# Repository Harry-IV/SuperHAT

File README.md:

# SuperHAT V2

A HAT (hardware attached on top) for the Raspberry Pi 4 & 5. 

---

## Power Rail Breakdown

SuperHAT receives external 5V and 12V power (with a common ground) from an [MR30 connector](https://www.tme.com/us/en-us/details/mr30pw-m/dc-power-connectors/amass/). 12V is used for tools and motors. 5V is used for tools, servos, and powering the Raspberry Pi. When using the SuperHAT, do not plug in a USB-C power supply. 

---

## Feature Overview

1. **Four** N-type MOSFETs for GPIO switching 5V or 12V tools.
2. **Six** connectors for I²C interfacing.
3. **One** dual H-bridge 12V motor driver.
4. **One** stepper motor driver
5. **Two** 5V servo connectors
6. Overvoltage Protection
7. Voltage & Current Sensing

### 1. MOSFET GPIO Switching

#### Schematic

#### N-Type MOSFET

The N-type MOSFET ([AOSS32136C](https://www.digikey.com/en/products/detail/alpha-omega-semiconductor-inc/AOSS32136C/11567433)) in the schematic is routed for low-side switching. When testing, switching on the high side (before the load), resulted in a voltage drop. In an underwater environment, employing low-side switching means that the wires leading to the tool will be high (5V or 12V) when the tool is idling. 

#### Back-EMF Protection

There is a standard diode ([GSD2004WS-HE3-08](https://www.digikey.com/en/products/detail/vishay-general-semiconductor-diodes-division/GSD2004WS-HE3-08/4831745?s=N4IgjCBcpgbFoDGUBmBDANgZwKYBoQB7KAbRABYAGSgJnIgKtoHZmQBdAgBwBcoQAyjwBOASwB2AcxABfArACcCEMkjps%2BIqQqUFAZn0dufSIJETpckAFZmlZavW4CxSGSrN9ADiMhe-ITEpWQIwBVYHVExnLTcQPTgFMBpff1NAixDwBS8laBUojRdte3YrGhpYCHzHaM1XMjAAAgA1JoABJrBqJoBbAEFUkxAAYUIAVy4MHAATAFVxUR4AeRQAWRw0LHHhHCyAWngaqBFx%2Bu0UsoJ9lOPIU-O46w4Zcu0Z0UIZvbKgA)) on the 5V and 12V lines. When the load is switched off, the diode prevents sensitive electronic components (the MOSFET in this case) from receiving voltage spikes generated by an inductive load (e.g. motor). 

#### 5V Configuration

To use a 5V you will need to solder the jumper (on the back of the board). Do not use a 12V tool when you solder the jumper because the 12V and 5V lines will short (because JP7 is closed and D3 leads to 5V). Technically, since MOSFETs can behave like variable resistors, and sending a PWM signal can "adjust" the voltage of the gate, it is possible to operate lower voltage tools. However, this is not recommended as there is no RC-filter at the gate to smooth these pulses. This RC-filter will be a feature in SuperHAT V3.

#### LED Indicator & Pulldown Resistor

In the schematic, there is an additional 10k $\Omega$ pulldown resistor in parallel with the LED circuit. This is because the LED can’t instantly pull down the voltage (since LEDs are non-ohmic). Intuitively, the green LED turns on when the GPIO is high. 

### 2. I²C Interfacing

#### Schematic

#### Connectors

To ensure connectivity with a wide range of devices, there are six "I²C connectors": two [right-angle JST-SH](https://www.digikey.com/en/products/detail/jst-sales-america-inc/SM04B-SRSS-TB/926710), two [vertical JST-SH](https://www.digikey.com/en/products/detail/jst-sales-america-inc/BM04B-SRSS-TB/926696), and two [right-angle JST-GH](https://www.digikey.com/en/products/detail/jst-sales-america-inc/SM04B-GHS-TB/807788) connectors. Note that JST-SH is  the same as STEMMA QT by Adafruit and Qwiic by Sparkfun. 

#### Pull-ups

There are no pullups for I²C on SuperHAT because the Raspberry Pi already incorporates 1.8k $\Omega$ pull-up resistors for SCL and SDA lines. 

#### 5V Device Support

Connector J10 is specifically designed for 5V I²C devices. While this connector provides 5V power to the device, the SDA and SCL logic lines remain at 3.3V levels. Ensure connected devices are 3.3V logic-compatible or include appropriate level-shifting circuitry.

### 3. Dual H-Bridge Motor Driver

#### Schematic

#### Operation

A 12V brushed DC motor can be driven in both directions with the [DRV8871](https://www.digikey.com/en/products/detail/texas-instruments/DRV8871DDARQ1/7244177?s=N4IgTCBcDaICICUBqAOFB2AjHOBBBAipiALoC%2BQA) motor driver. Input pins are set to GPIOs 9 and 10. To drive the motor, set one of the pins to high, and the other to low. Flip the status of both pins to drive the motor in the opposite direction. The motor won't move went both GPIOs are set to low. The 30k $\Omega$ resistor on pin 4 (ILIM) results in a trip current of about 2A (64 (kV) / R<sub>ILIM</sub> (k $\Omega$)). 

### 4. Stepper Motor Driver

#### Schematic

#### Operation

A 12V stepper motor can be driven by this motor driver ([DRV8825](https://www.digikey.com/en/products/detail/texas-instruments/DRV8825PWPR/2695909)). The pins for operation are GPIOs 21 and 26. Pulse GPIO 21 to move the stepper motor and set GPIO 26 to low or high to determine the direction of rotation. To test the stepper motor, run this code: https://github.com/Harry-IV/superhat_test/blob/main/stepper_motor.py.

#### Settings

To adjust the current limiting, use the screwhead on the potentiometer. The current limit is the voltage read on the screw head of the potentiometer multiplied by 2. To disable the stepper motor driver, solder jumper JP6. 

#### Cooling

This IC gets hot, especially at higher currents. It would be wise to put a heat-sink.

### 5. Servo Driving

#### Schematic

#### Operation

GPIOs 12 and 13 can each drive one servo motor (a total of two for SuperHAT). Having a direct connection, especially with a Raspberry Pi due to their timing inconsistencies, can lead to jitter. This can be mitigated by using the [pigpio library](https://abyz.me.uk/rpi/pigpio/) or by "sleeping" the pin while not moving the servo. 

### 6. Overvoltage Protection

#### Schematic

#### Undervoltage Lockout (UVLO)

The [TPS259621](https://www.digikey.com/en/products/detail/texas-instruments/TPS259621DDAR/10445382) will cut off power to the Raspberry Pi completely if the EN/UVLO pin does not receive a voltage above 1.2V (when rising). The UVLO threshold is set by a voltage divider consisting of resistors R18 (7.5kΩ) and R19 (2.61kΩ). These values yield an undervoltage cutoff of 4.85V. Note that the undervoltage cutoff when falling will be lower since it will cut off when the EN/UVLO pin does not receive a voltage above 1.1V. Ultimately, this part of the circuit isn’t really that necessary.

#### Overvoltage Clamping

What is more necessary is the overvoltage component. Here, there is no voltage divider. Texas Instrument's documentation calls for a 400k ohm resistor for the output clamp voltage to be 5.45V, but a 470k ohm resistor is used instead because they are a lot easier to come by. 

#### Additional Resources

Video explanation by GreatScott!: https://www.youtube.com/watch?v=JOhQ3nsR7xo&t=440s 

### 7. Voltage and Current Sensing

#### Schematic

#### INA3221

The [INA3221](https://www.digikey.com/en/products/detail/texas-instruments/INA3221AQRGVRQ1/5995432) is a digital power-sensing IC that communicates via I²C. It features 3 channels, which are used to measure the voltage and current on the 3.3V, 5V, and 12V rails. 

#### Shunt Resistors

Two 0.04 Ω resistors are placed at the 5V and 12V lines near the MR30 connector. All 5V and 12V power on the SuperHAT flows through these two shunts. This includes power draw at 5V from the Pi. A third 0.04 Ω resistor is placed on the 3.3V line near the 3.3V pin from the Raspberry Pi. This does not measure how much current the Pi draws at 3.3V, but rather how much SuperHAT draws (with I²C devices mainly).

#### Testing

To test the INA3221, run this code, which uses Adafruit's INA3221 library: [https://github.com/Harry-IV/superhat_test/tree/main/INA3221]

---

## PCB Layout

### 4-layer Stackup

| Layer | Type                      |
| ----- | ------------------------- |
| 1     | Signal                    |
| 2     | Ground                    |
| 3     | Power (3.3V, 5V, 12V)     |
| 4     | Signal                    |

### Design Notes

* Via-in-pad is used to condense routing.
* Copper pours help with thermal dissipation.

---

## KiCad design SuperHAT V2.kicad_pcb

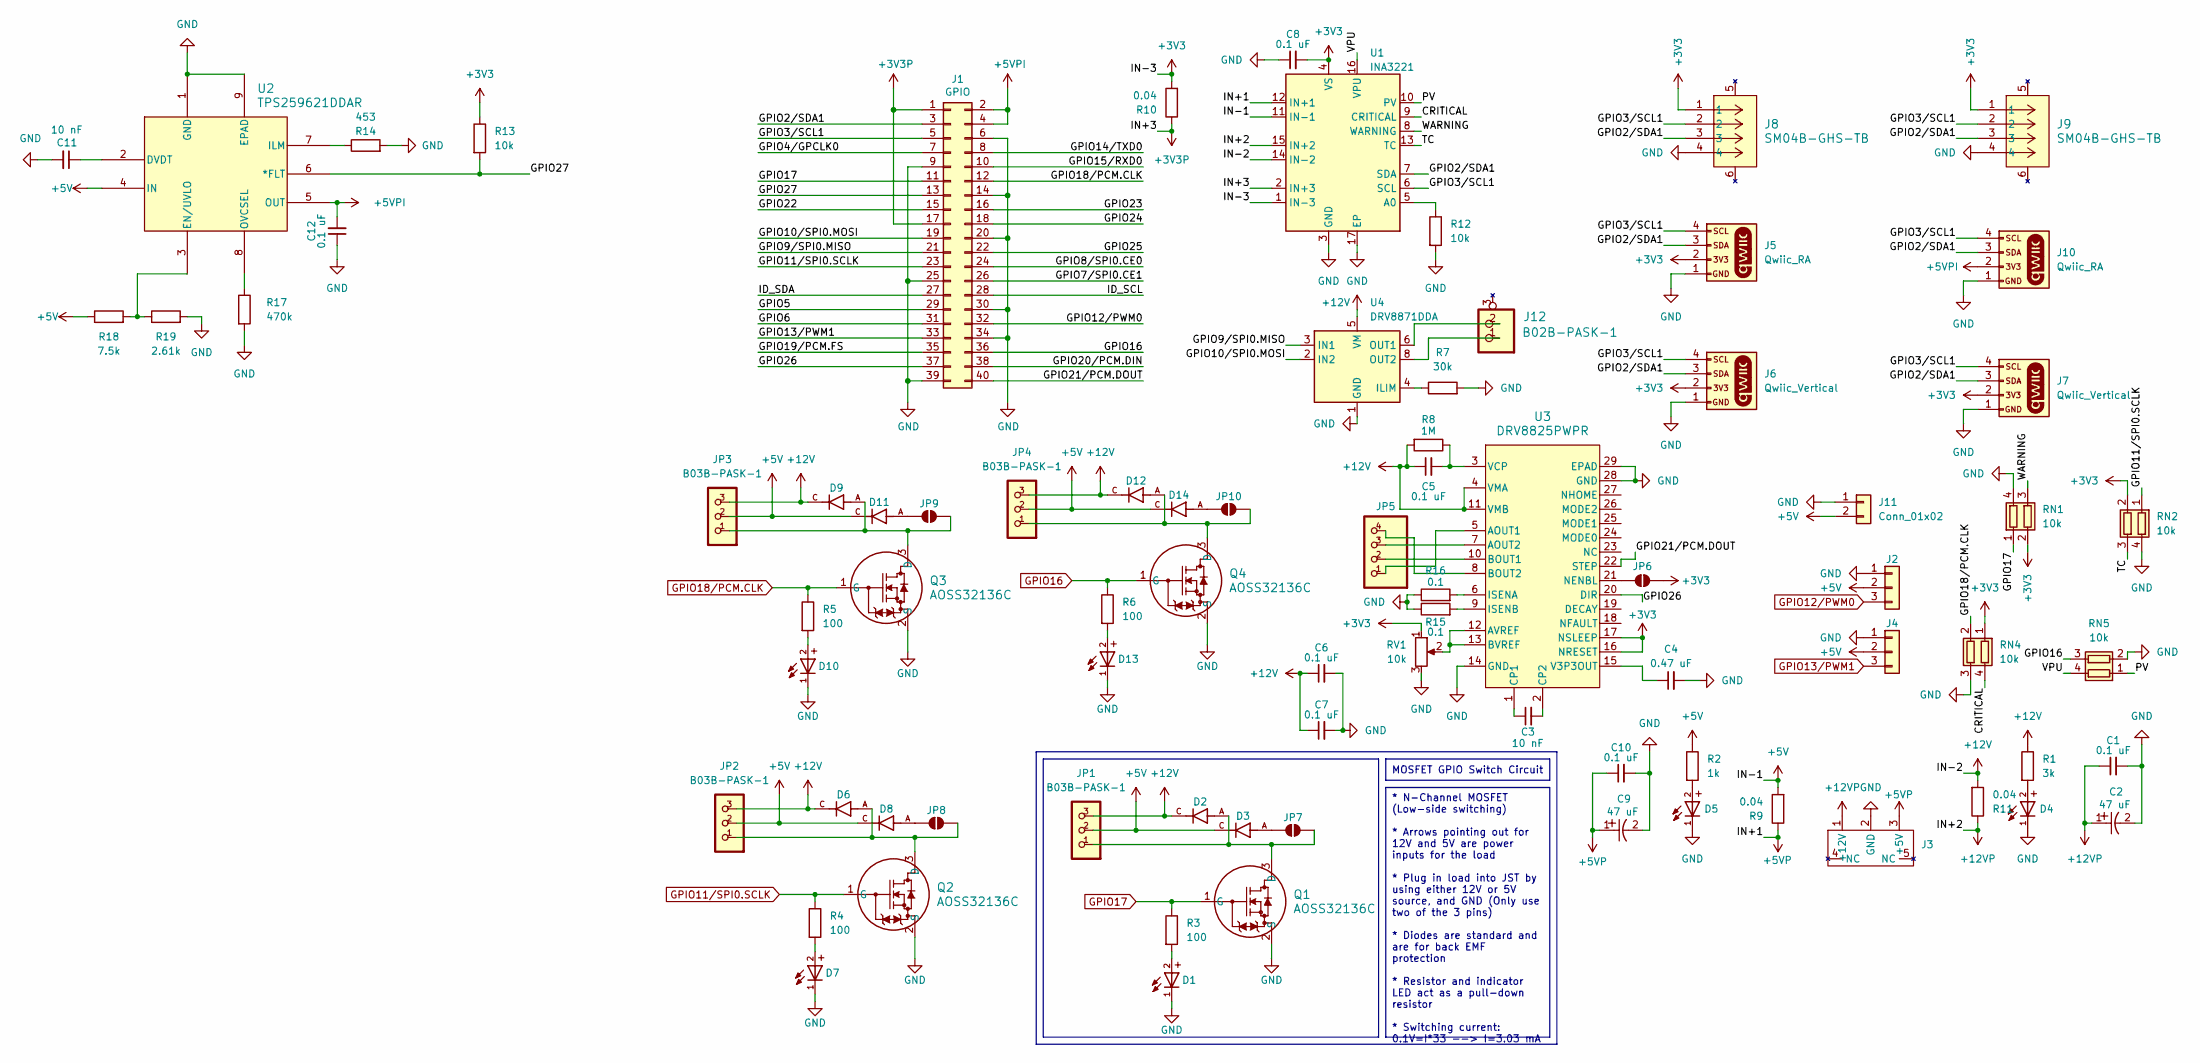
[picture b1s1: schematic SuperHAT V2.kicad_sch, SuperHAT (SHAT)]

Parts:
C1, C5, C6, C7, C8, C10, C12: 0.1 uF; CAPC2012X140N; Part # C0805C104J5RACAUTO
C2, C9: 47 uF; CAPMP7.6X4.3_3.1N_KEM; Part # T598D476M025ATE060
C3, C11: 10 nF; CAPC2012X140N; Part # C0805C103K5TACAUTO
C4: 0.47 uF; CAPC2012X140N; Part # C0805C474J9RACTU
D1, D7, D10, D13: WL-SMCW_0805; Part # 150080GS75000
D2, D3, D6, D8, D9, D11, D12, D14: SOD2613X115N; Part # GSD2004WS-HE3-08
D4, D5: WL-SMCW_0805; Part # 150080RS75000
J1: GPIO; PinSocket_2x20_P2.54mm_Vertical; Part # PRT-14017
J2, J4: Conn_01x03; PinHeader_1x03_P2.54mm_Vertical; Part # 61300311121
J3: AMASS_MR30PW-M_1x03_P3.50mm_Horizontal; Part # MR30PW-M
J5, J10: Qwiic_RA; QWIIC Connector RA; Part # SM04B-SRSS-TB
J6, J7: Qwiic_Vertical; JST_SMD_1.0mm-4_Vertical; Part # BM04B-SRSS-TB
J8, J9: SM04B-GHS-TB; CONN_SM04B-GHS-TB_JST; Part # SM04B-GHS-TB
J11: Conn_01x02; PinHeader_1x02_P2.54mm_Horizontal; Part # 10129379-902002BLF
J12: B02B-PASK-1; CONN_B02B-PASK-1_JST; Part # B02B-PASK-1
JP1, JP2, JP3, JP4: B03B-PASK-1; Part # B03B-PASK-1
JP5: B04B-PASK-1; Part # B04B-PASK-1
JP6, JP7, JP8, JP9, JP10: SolderJumper_2_Open; SolderJumper-2_P1.3mm_Open_TrianglePad1.0x1.5mm
Q1, Q2, Q3, Q4: AOSS32136C; SOT23_AOS; Part # AOSS32136C
R1: 3k; RES_TNPW0805_VIS; Part # TNPW08053K00BEEA
R2: 1k; RES_TNPW0805_VIS; Part # TNPW08051K00BEEA
R3, R4, R5, R6: 100; RES_CHP0805_BRN; Part # CHP0805AFX-1000ELF
R7: 30k; RESC2012X60N; Part # SG73S2ATTD3002F
R8: 1M; RES_CMP0805_BRN; Part # CMP0805AFX-1004ELF
R9, R10, R11: 0.04; RES_VISHAY_WSLP0805_VIS; Part # WSLP0805R0400DEA
R12, R13: 10k; RES_CHP0805_BRN; Part # CHP0805AFX-1002ELF
R14: 453; RESC2012X60N; Part # RN73R2ATTD4530B25
R15, R16: 0.1; RES_VISHAY_WSLP0805_VIS; Part # WSLP0805R1000FEA
R17: 470k; RES_CMP0805_BRN; Part # CMP0805AFX-4703ELF
R18: 7.5k; RES_TNPW0805_VIS; Part # TNPW08057K50BEEA
R19: 2.61k; RES_TNPW0805_VIS; Part # TNPW08052K61BEEN
RN1, RN2, RN4, RN5: 10k; SMT_1002P1AT_VIS; Part # ACASN1002S1002P1AT
RV1: 10k; POT_TC33_3X3P8_BRN; Part # TC33X-1-103ETC33X-1-103E
U1: INA3221; Texas_RGV0016A_VQFN-16-1EP_4x4mm_P0.65mm_EP2.1x2.1mm; Part # INA3221AQRGVRQ1
U2: TPS259621DDAR; SOIC_20DDAR_TEX; Part # TPS259621DDAR
U3: DRV8825PWPR; PWP28_5P18X3P1; Part # DRV8825PWPR
U4: DRV8871DDA; Texas_HTSOP-8-1EP_3.9x4.9mm_P1.27mm_EP2.95x4.9mm_Mask2.4x3.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; Part # DRV8871DDARQ1

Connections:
+3V3: C8.2, J5.2, J6.2, J7.2, J8.1, J9.1, JP6.2 (B), R10.2, R13.1, RN1.2 (R2.1), RN2.2 (R2.1), RN4.1 (R1.1), RV1.1, U1.1 (IN-3), U1.4 (VS), U3.16 (NRESET), U3.17 (NSLEEP)
+3V3P: J1.1, J1.17, R10.1, U1.2 (IN+3)
+5V: D3.C, D8.C, D11.C, D14.C, J2.2, J4.2, J11.2, JP1.2, JP2.2, JP3.2, JP4.2, R2.1, R9.2, R18.1, U1.11 (IN-1), U2.4 (IN)
+5VP: C9.1, C10.1, J3.3 (+5V), R9.1, U1.12 (IN+1)
+5VPI: C12.2, J1.2, J1.4, J10.2, U2.5 (OUT)
+12V: C5.1, C6.1, C7.1, D2.C, D6.C, D9.C, D12.C, JP1.3, JP2.3, JP3.3, JP4.3, R1.1, R8.2, R11.2, U1.14 (IN-2), U3.4 (VMA), U3.11 (VMB), U4.5 (VM)
+12VP: C1.1, C2.1, J3.1 (+12V), R11.1, U1.15 (IN+2)
/CRITICAL: RN4.4 (R1.2), U1.9 (CRITICAL)
/GPIO2/SDA1: J1.3, J5.3, J6.3, J7.3, J8.3, J9.3, J10.3, U1.7 (SDA)
/GPIO3/SCL1: J1.5, J5.4, J6.4, J7.4, J8.2, J9.2, J10.4, U1.6 (SCL)
/GPIO4/GPCLK0: J1.7
/GPIO5: J1.29
/GPIO6: J1.31
/GPIO7/SPI0.CE1: J1.26
/GPIO8/SPI0.CE0: J1.24
/GPIO9/SPI0.MISO: J1.21, U4.3 (IN1)
/GPIO10/SPI0.MOSI: J1.19, U4.2 (IN2)
/GPIO14/TXD0: J1.8
/GPIO15/RXD0: J1.10
/GPIO19/PCM.FS: J1.35
/GPIO20/PCM.DIN: J1.38
/GPIO21/PCM.DOUT: J1.40, U3.22 (STEP)
/GPIO22: J1.15
/GPIO23: J1.16
/GPIO24: J1.18
/GPIO25: J1.22
/GPIO26: J1.37, U3.20 (DIR)
/GPIO27: J1.13, R13.2, U2.6 (*FLT)
/ID_SCL: J1.28
/ID_SDA: J1.27
/PV: RN5.1 (R1.1), U1.10 (PV)
/TC: RN2.3 (R2.2), U1.13 (TC)
/VPU: RN5.4 (R1.2), U1.16 (VPU)
/WARNING: RN1.3 (R2.2), U1.8 (WARNING)
GND: C1.2, C2.2, C4.2, C6.2, C7.2, C8.1, C9.2, C10.2, C11.2, C12.1, D1.1, D4.1, D5.1, D7.1, D10.1, D13.1, J1.6, J1.9, J1.14, J1.20, J1.25, J1.30, J1.34, J1.39, J2.1, J3.2 (GND), J4.1, J5.1, J6.1, J7.1, J8.4, J9.4, J10.1, J11.1, Q1.2 (S), Q2.2 (S), Q3.2 (S), Q4.2 (S), R7.2, R12.2, R14.2, R15.1, R16.1, R17.2, R19.2, RN1.4 (R1.2), RN2.4 (R1.2), RN4.3 (R2.2), RN5.2 (R2.1), RV1.3, U1.3 (GND), U1.17 (EP), U2.1 (GND), U2.9 (EPAD), U3.14 (GND), U3.28 (GND), U3.29 (EPAD), U4.1 (GND), U4.7 (GND), U4.9 (GND)
GPIO11/SPI0.SCLK: J1.23, Q2.1 (G), R4.1, RN2.1 (R1.1)
GPIO12/PWM0: J1.32, J2.3
GPIO13/PWM1: J1.33, J4.3
GPIO16: J1.36, Q4.1 (G), R6.1, RN5.3 (R2.2)
GPIO17: J1.11, Q1.1 (G), R3.1, RN1.1 (R1.1)
GPIO18/PCM.CLK: J1.12, Q3.1 (G), R5.1, RN4.2 (R2.1)
unnamed: D1.2, R3.2
unnamed: D4.2, R1.2
unnamed: D5.2, R2.2
unnamed: D7.2, R4.2
unnamed: D10.2, R5.2
unnamed: D13.2, R6.2
unnamed: JP6.1 (A), U3.21 (NENBL)
unnamed: D2.A, JP1.1, JP7.1 (A), Q1.3 (D)
unnamed: D3.A, JP7.2 (B)
unnamed: D6.A, JP2.1, JP8.1 (A), Q2.3 (D)
unnamed: D8.A, JP8.2 (B)
unnamed: D9.A, JP3.1, JP9.1 (A), Q3.3 (D)
unnamed: D11.A, JP9.2 (B)
unnamed: D12.A, JP4.1, JP10.1 (A), Q4.3 (D)
unnamed: D14.A, JP10.2 (B)
unnamed: R12.1, U1.5 (A0)
unnamed: C11.1, U2.2 (DVDT)
unnamed: R18.2, R19.1, U2.3 (EN/UVLO)
unnamed: R14.1, U2.7 (ILM)
unnamed: R17.1, U2.8 (OVCSEL)
unnamed: JP5.1, U3.5 (AOUT1)
unnamed: JP5.3, U3.7 (AOUT2)
unnamed: RV1.2, U3.12 (AVREF), U3.13 (BVREF)
unnamed: JP5.2, U3.10 (BOUT1)
unnamed: JP5.4, U3.8 (BOUT2)
unnamed: C3.1, U3.1 (CP1)
unnamed: C3.2, U3.2 (CP2)
unnamed: R16.2, U3.6 (ISENA)
unnamed: R15.2, U3.9 (ISENB)
unnamed: C4.1, U3.15 (V3P3OUT)
unnamed: C5.2, R8.1, U3.3 (VCP)
unnamed: R7.1, U4.4 (ILIM)
unnamed: J12.2, U4.6 (OUT1)
unnamed: J12.1, U4.8 (OUT2)

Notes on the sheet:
MOSFET GPIO Switch Circuit
* N-Channel MOSFET (Low-side switching) * Arrows pointing out for 12V and 5V are power inputs for the load * Plug in load into JST by using either 12V or 5V source, and GND (Only use two of the 3 pins) * Diodes are standard and are for back EMF protection * Resistor and indicator LED act as a pull-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

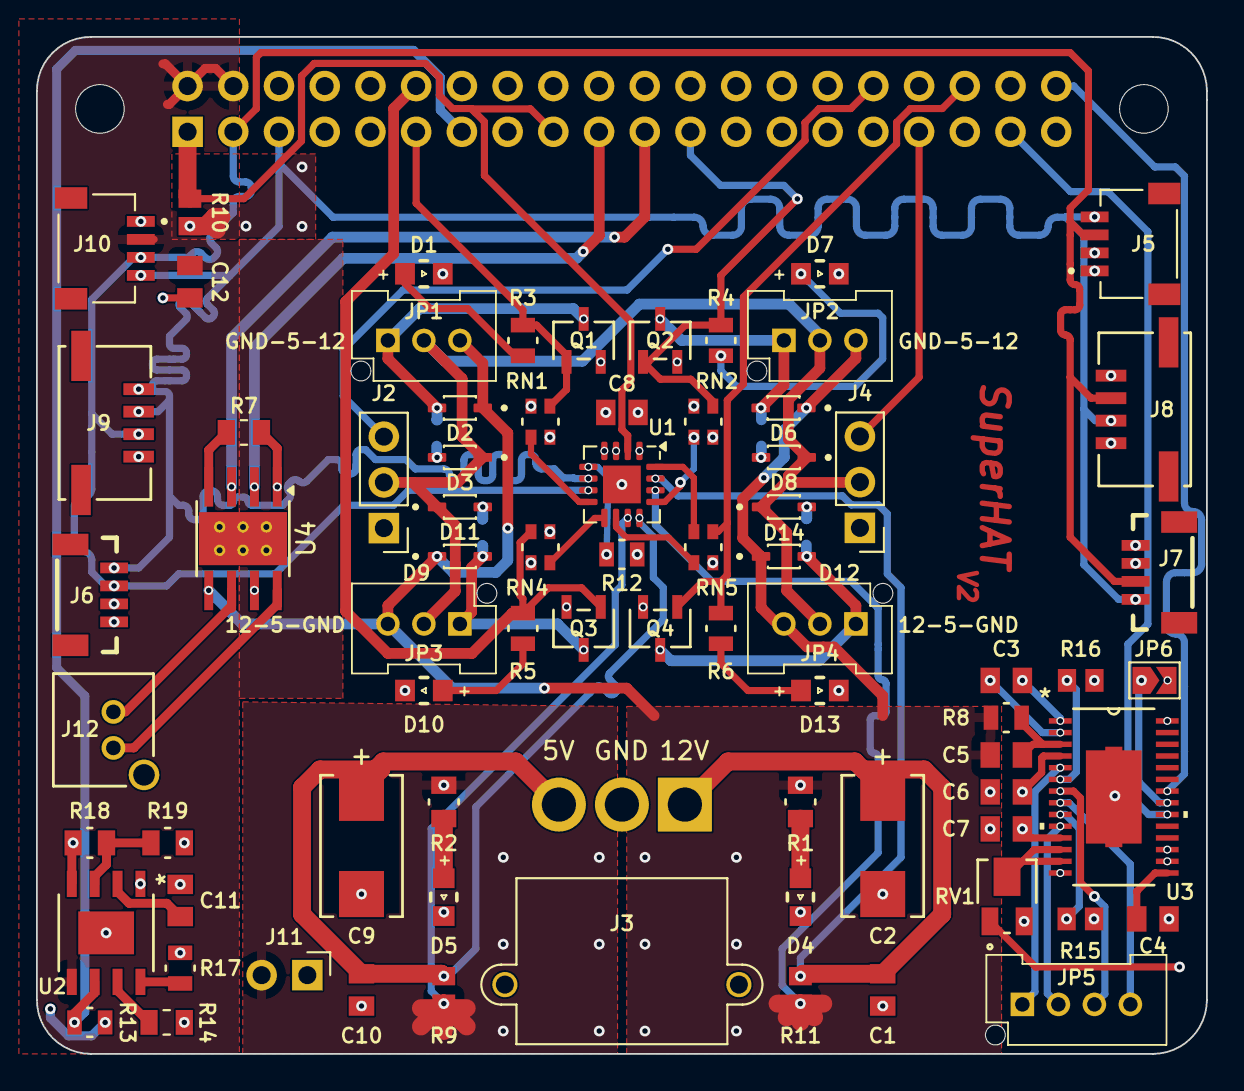
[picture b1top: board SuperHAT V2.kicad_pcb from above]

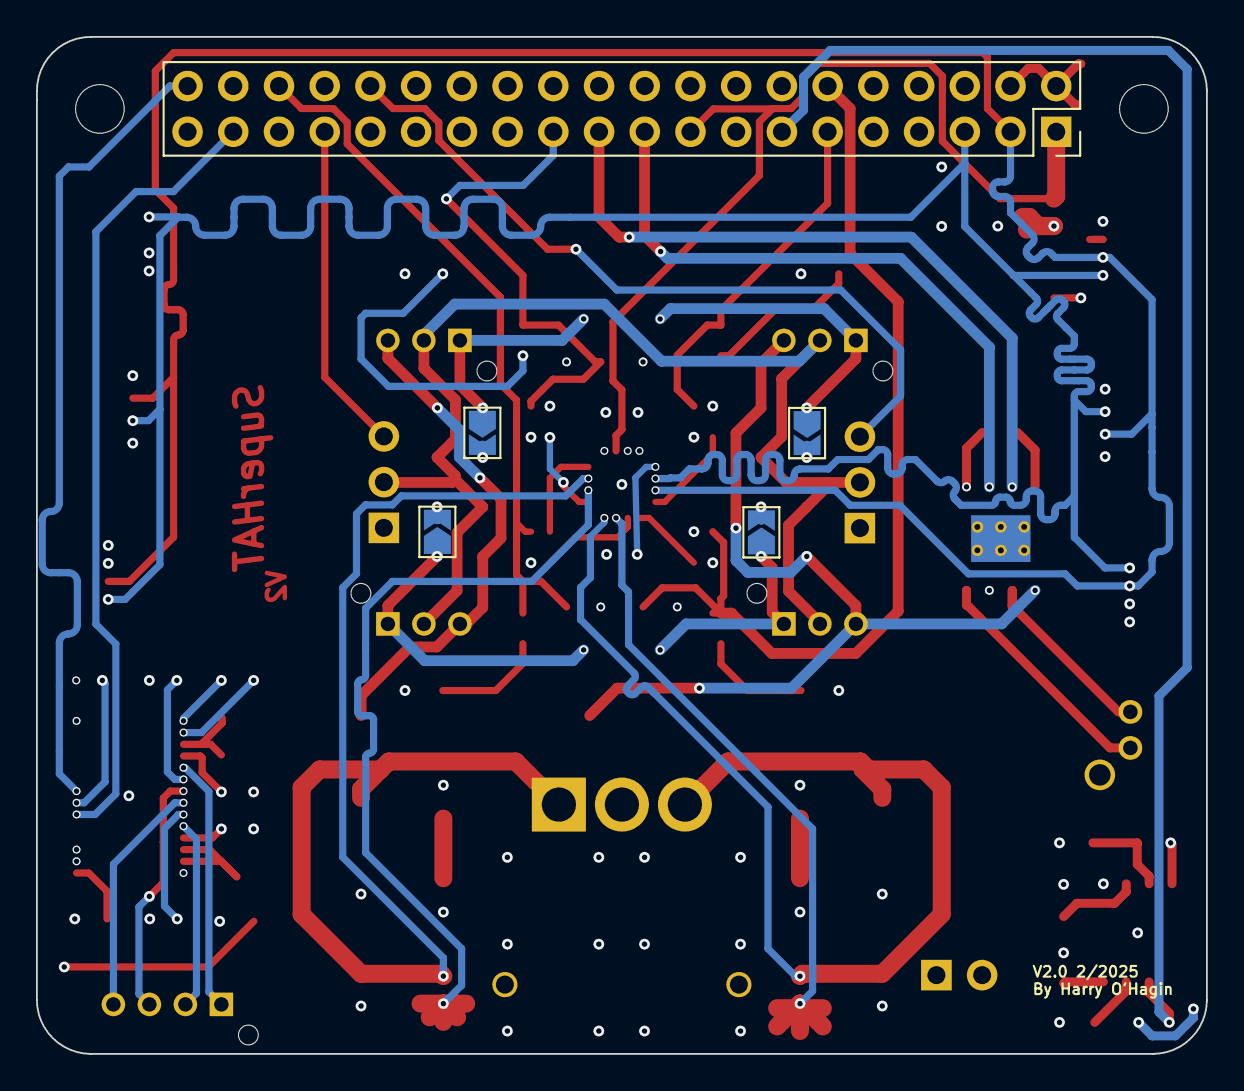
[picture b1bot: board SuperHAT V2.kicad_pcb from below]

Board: 4 copper layers, 65.0 x 56.5 mm, 82 parts (5 on the bottom side), 60 nets.

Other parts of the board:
MH1, MH2: MountingHole_2.7mm_M2.5

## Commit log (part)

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2024-12-29 First commit.
2024-12-29 Committing before creating HTML BOM, in case if it messes things up.
2024-12-29 No errors before generating BOM.
2024-12-29 Beautiful BOM.
2024-12-29 Modified 2x20 SMT header for stencil fabrication.
2025-02-16 SuperHAT before changes.
2025-02-16 Schematic changes made.
2025-02-17 Fixed MOSFET circuits, pin values, and diode layout.
2025-02-18 Added overvoltage protection to schematic.
2025-02-18 Overvoltage protection laid out on footprint.
2025-02-23 Pre footprint migration to create BOM V2
2025-02-23 Bom acting goofy but I still generated one.
2025-02-23 SuperHAT V2
2025-12-26 added .gitignore
2025-12-26 updated .gitignore
2025-12-27 Updated README
    Added detailed features and specifications for SuperHAT V2, including power rail breakdown, MOSFET GPIO switching, I²C interfacing, motor drivers, and voltage/current sensing.
2025-12-27 Add MIT License to the project
